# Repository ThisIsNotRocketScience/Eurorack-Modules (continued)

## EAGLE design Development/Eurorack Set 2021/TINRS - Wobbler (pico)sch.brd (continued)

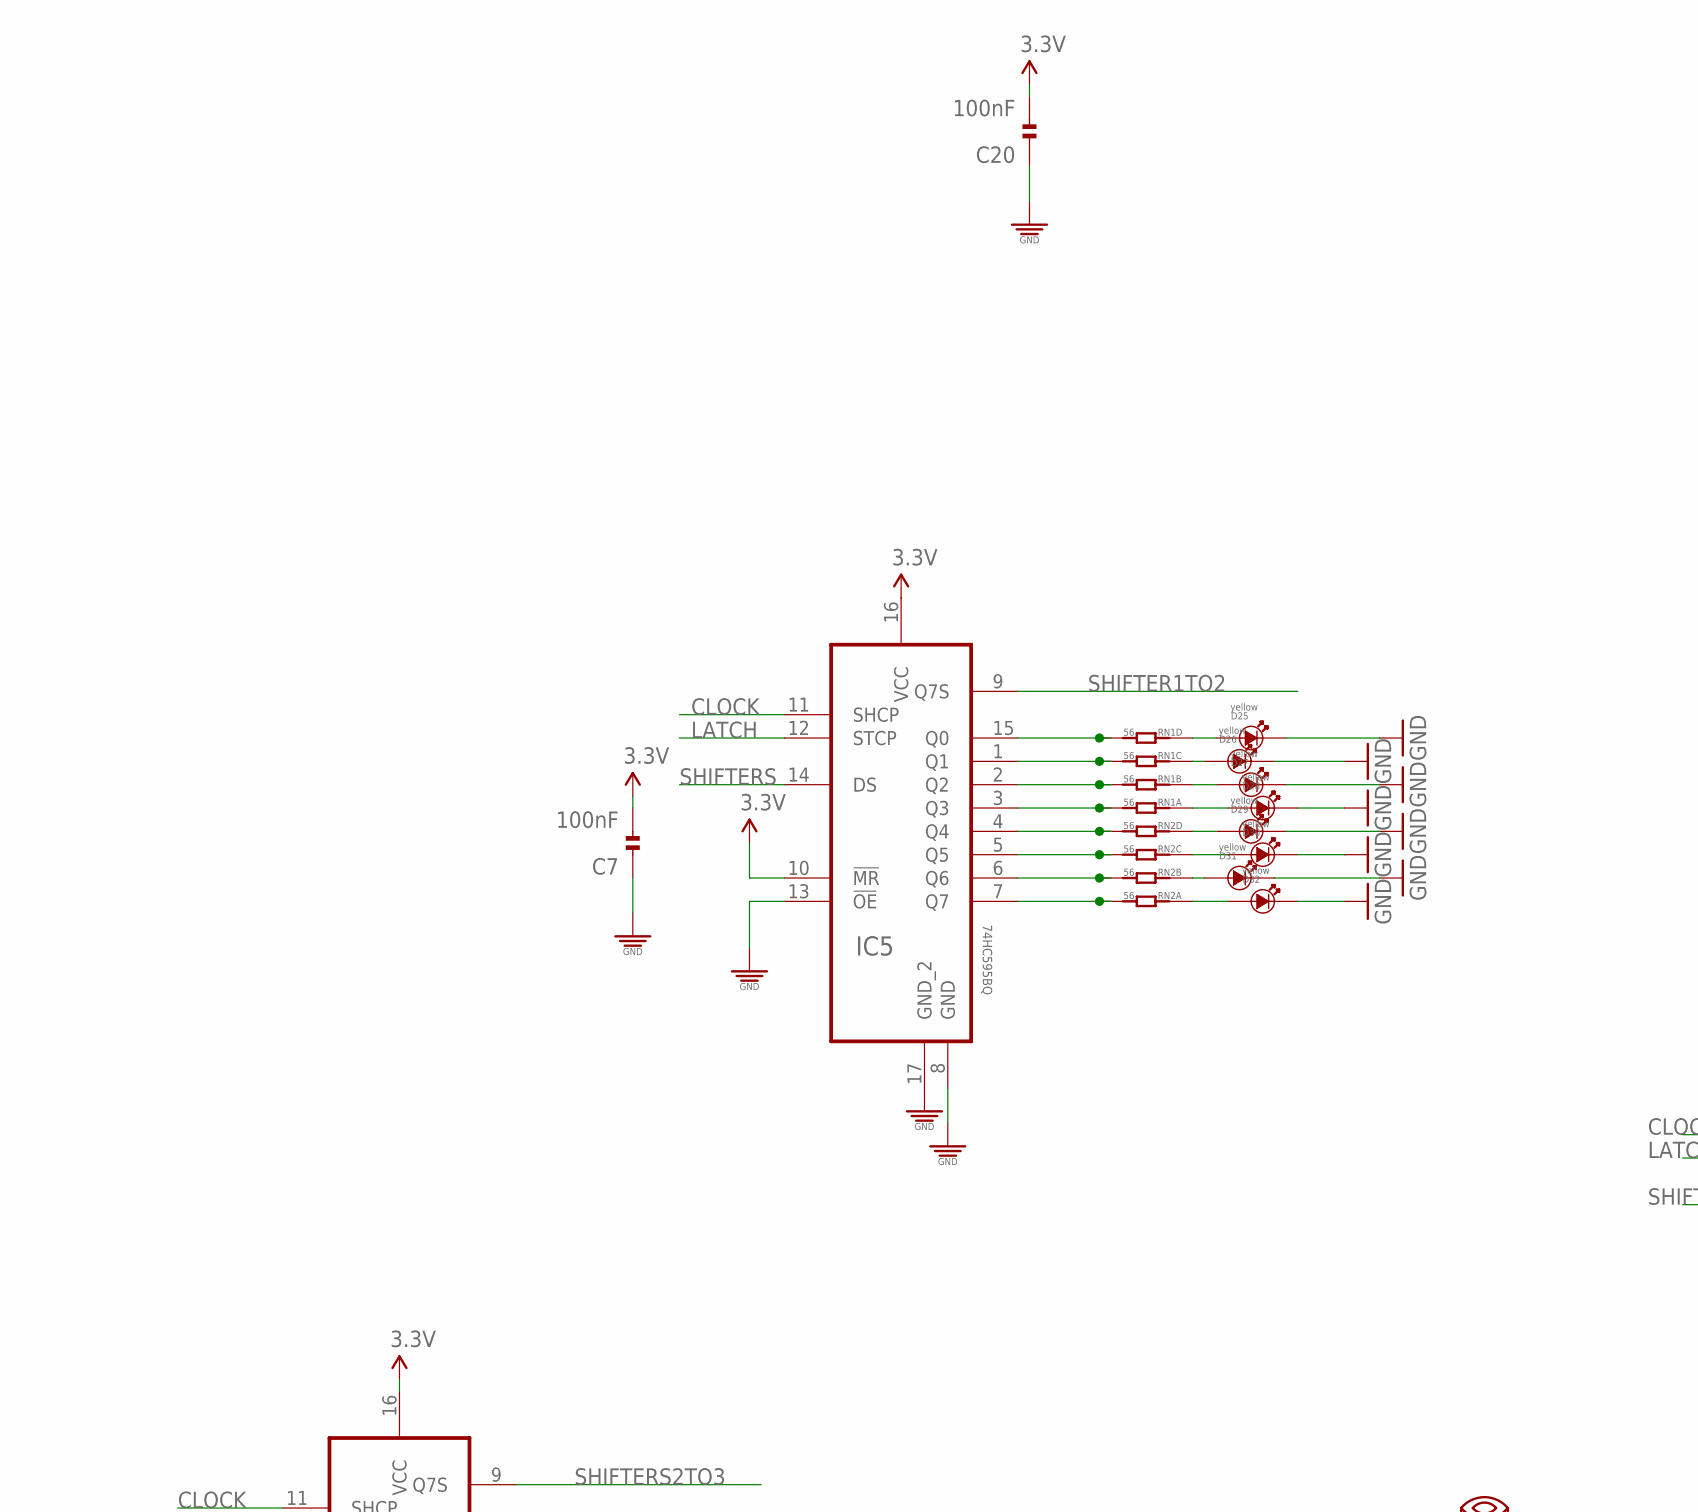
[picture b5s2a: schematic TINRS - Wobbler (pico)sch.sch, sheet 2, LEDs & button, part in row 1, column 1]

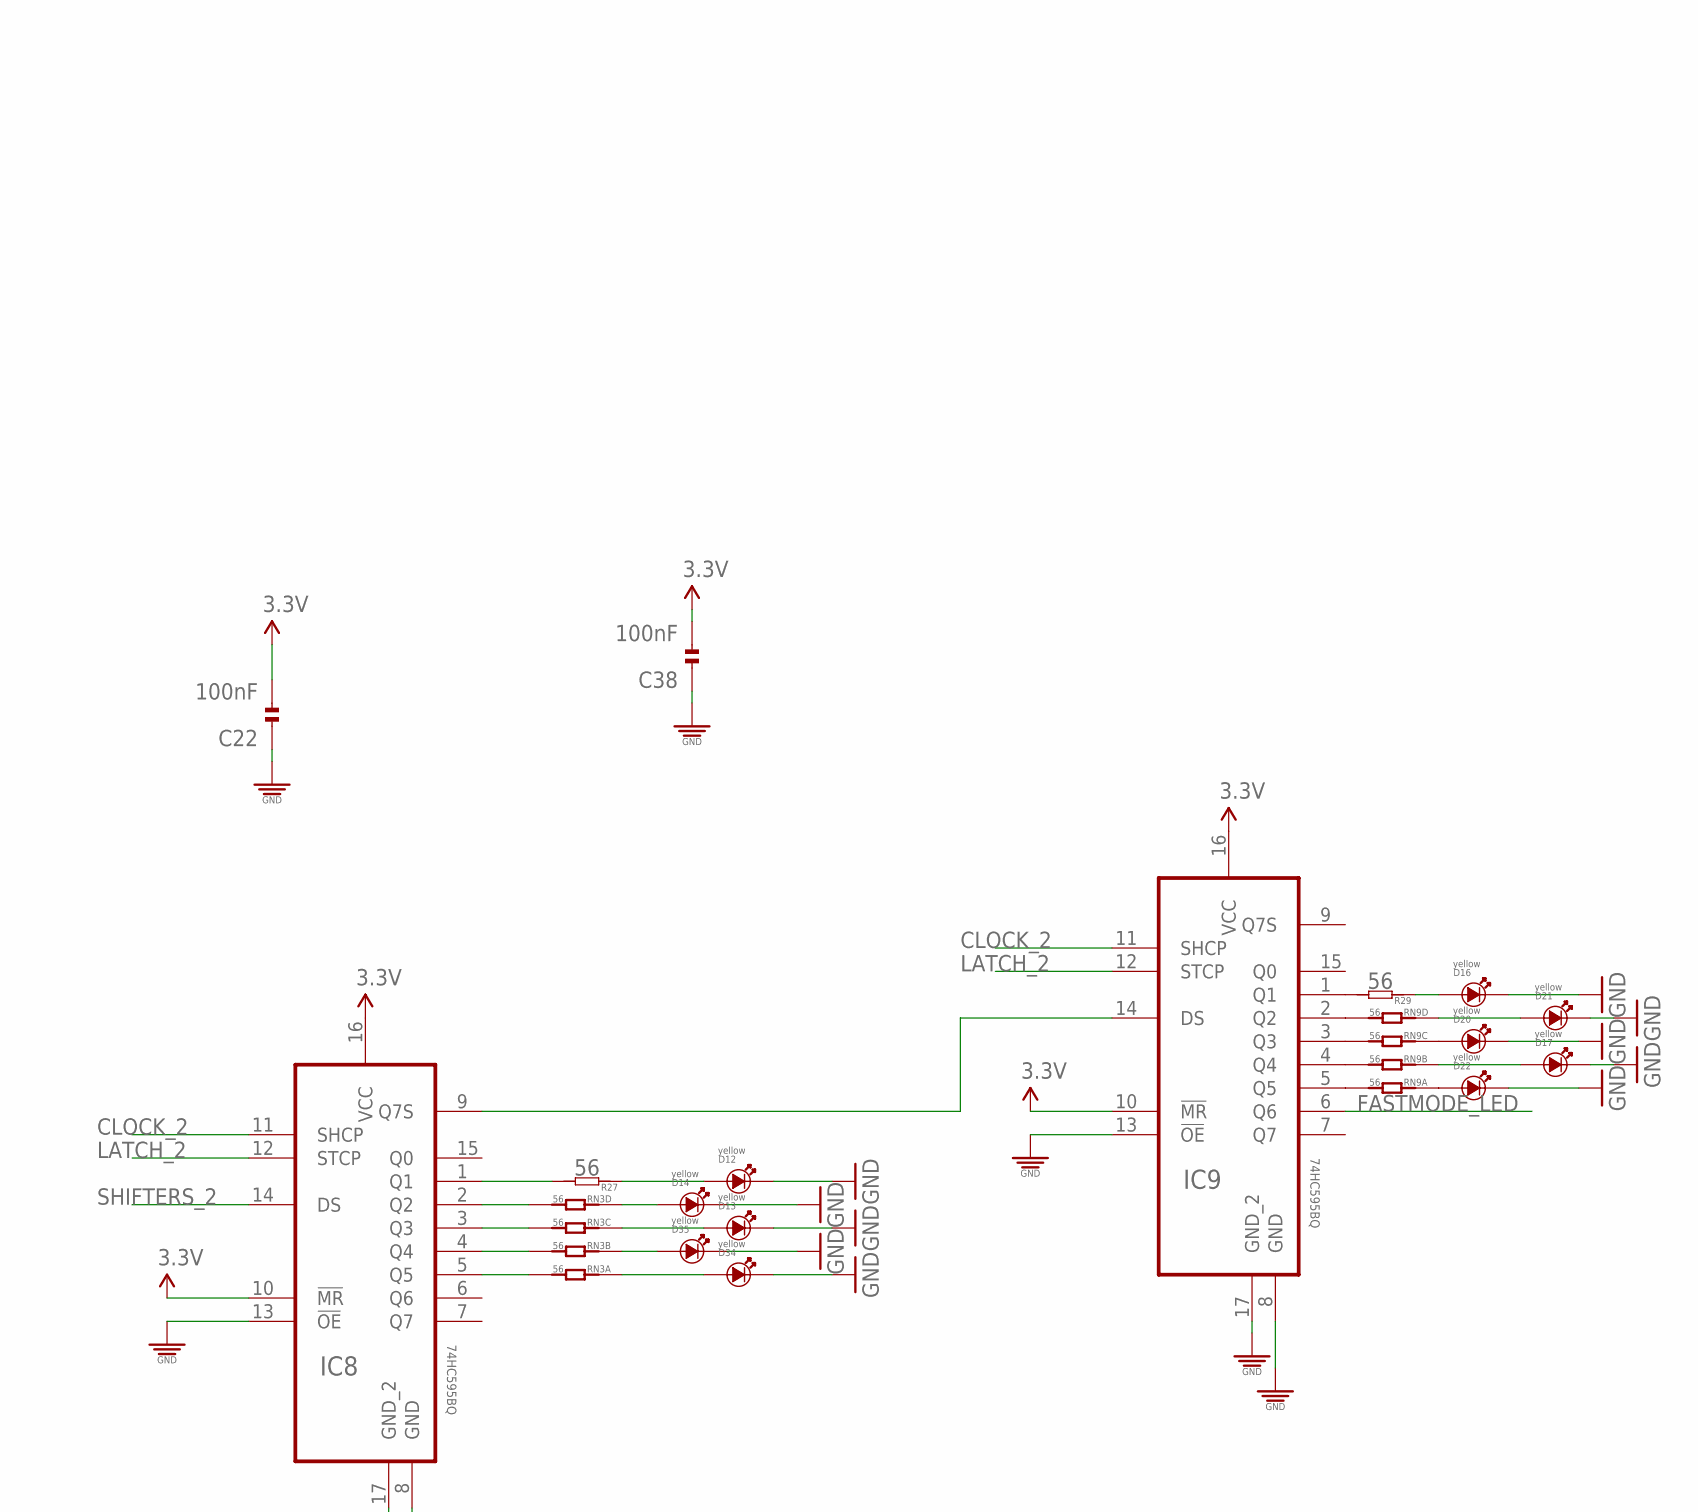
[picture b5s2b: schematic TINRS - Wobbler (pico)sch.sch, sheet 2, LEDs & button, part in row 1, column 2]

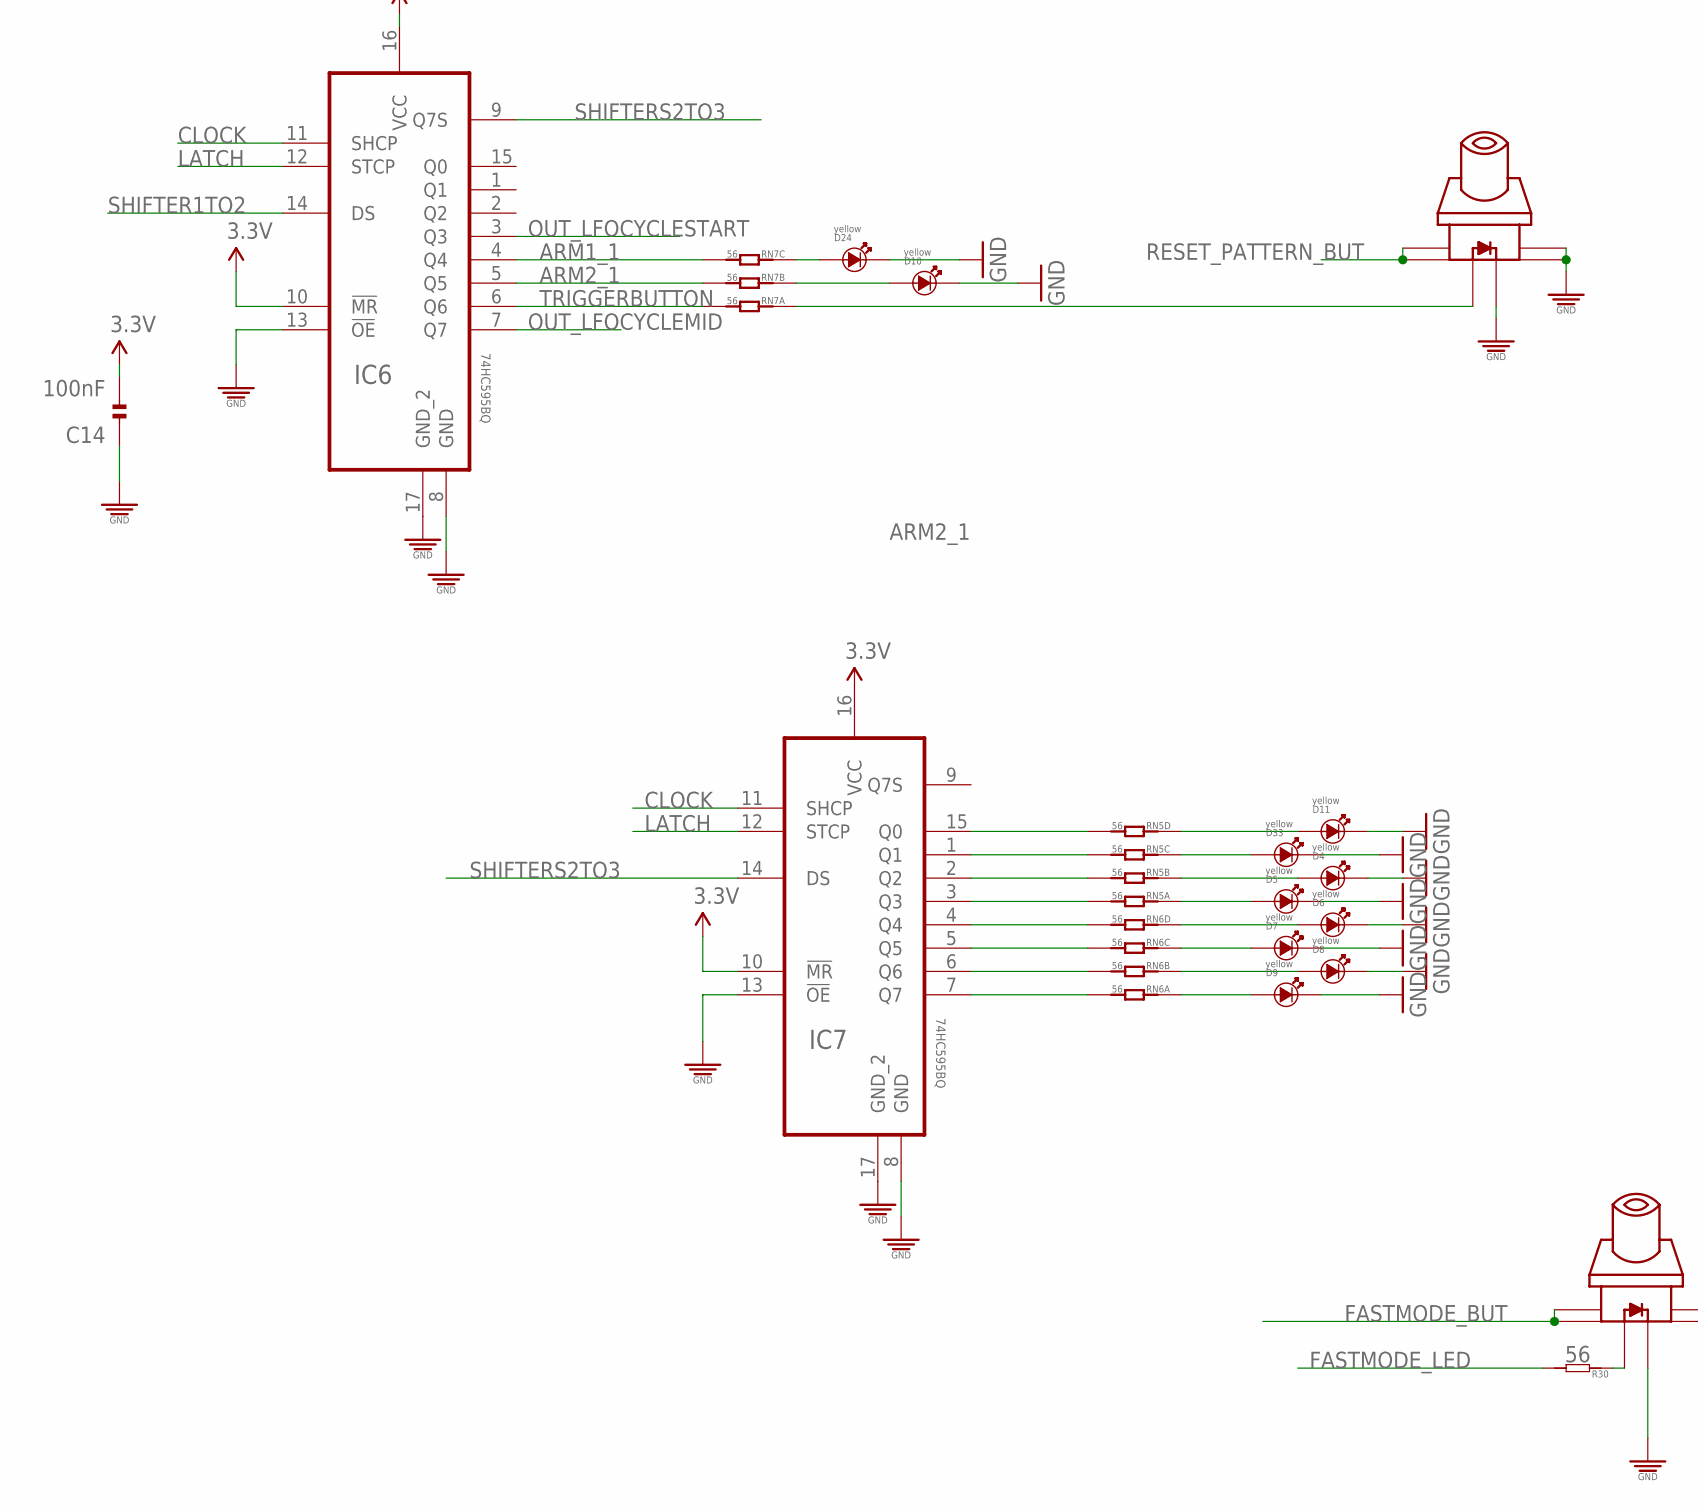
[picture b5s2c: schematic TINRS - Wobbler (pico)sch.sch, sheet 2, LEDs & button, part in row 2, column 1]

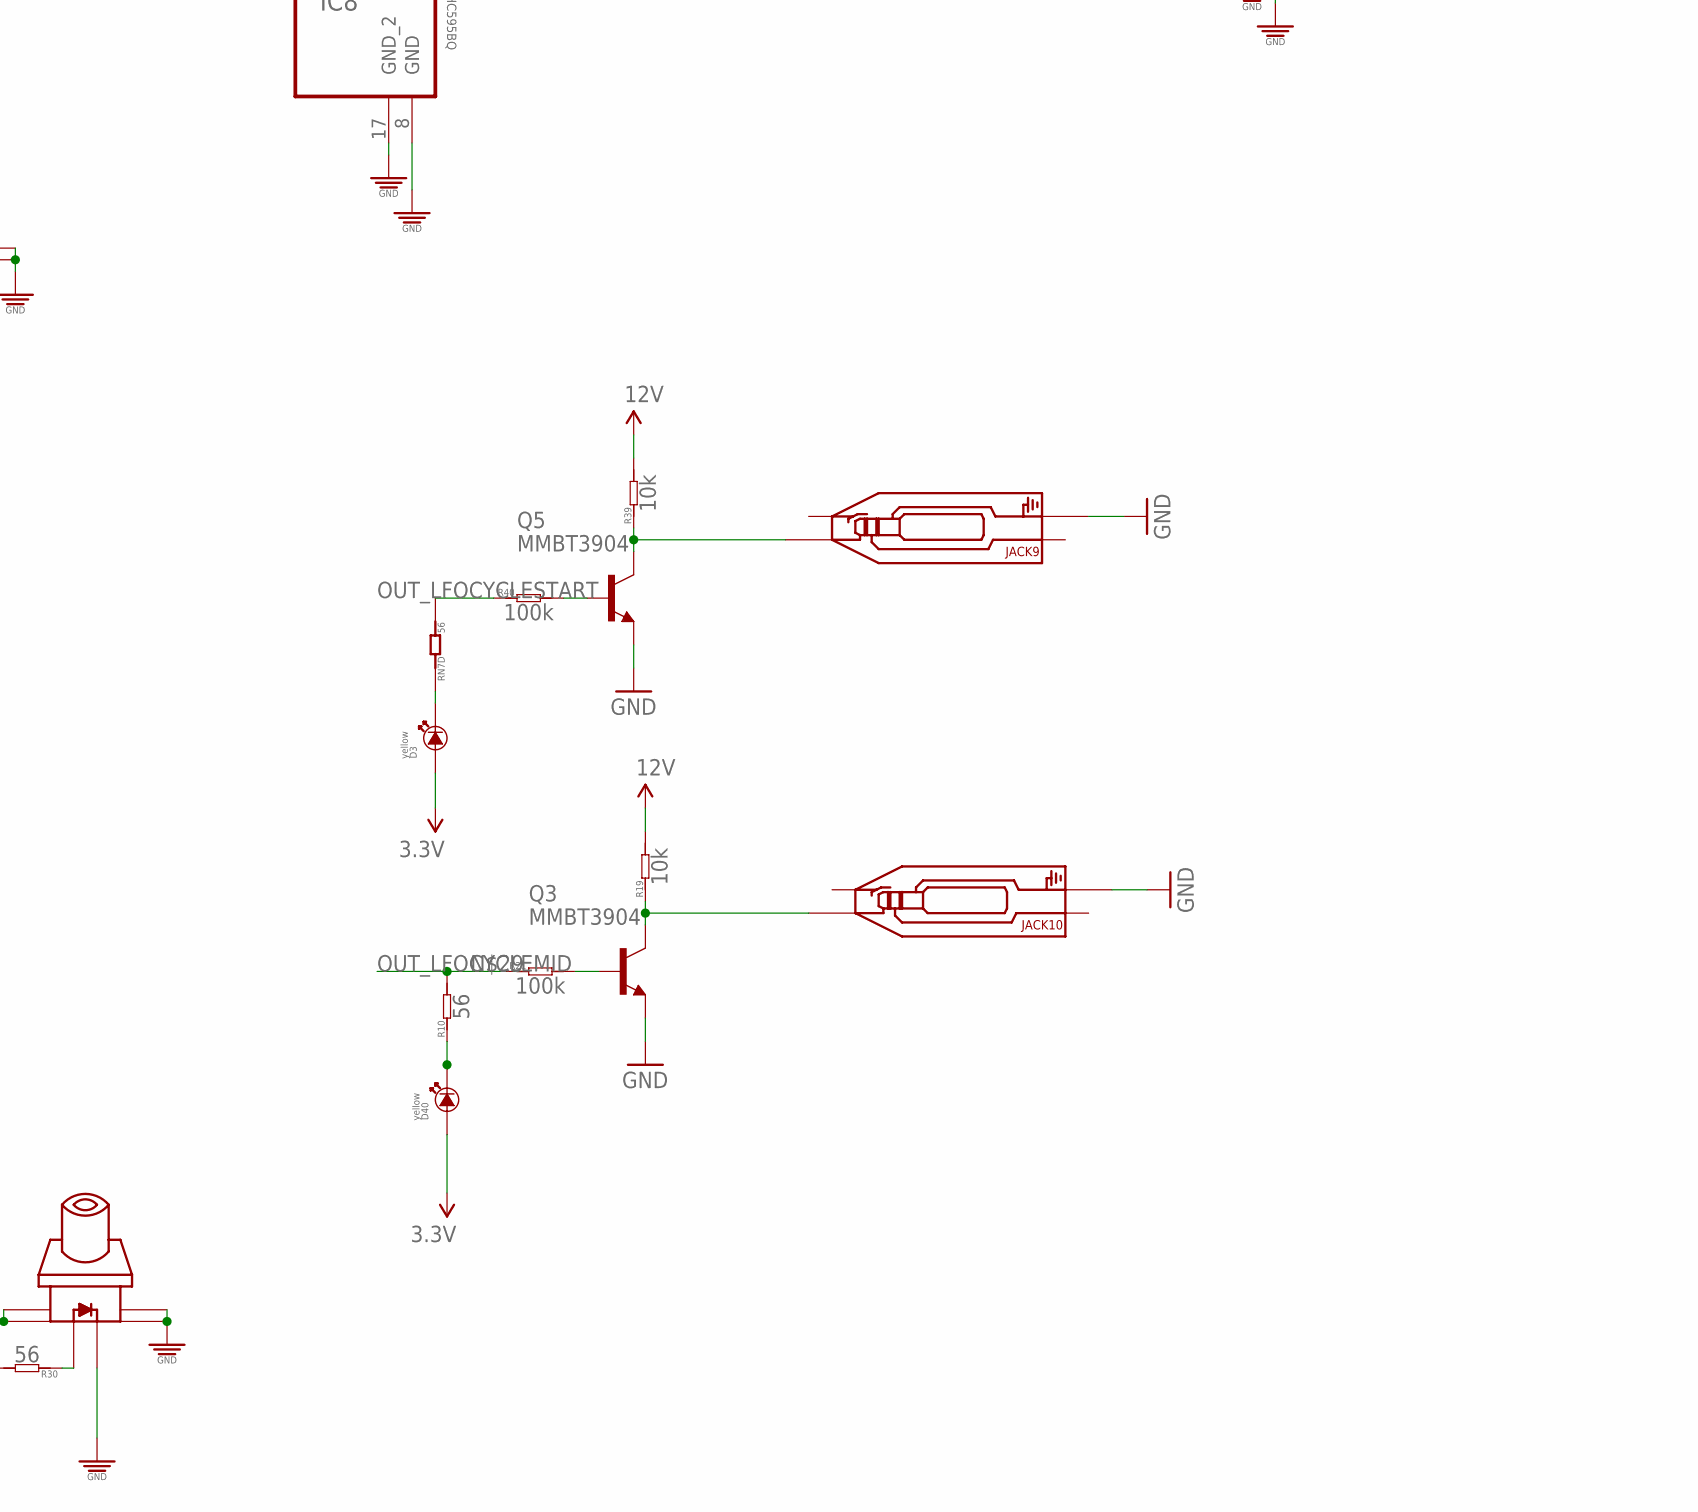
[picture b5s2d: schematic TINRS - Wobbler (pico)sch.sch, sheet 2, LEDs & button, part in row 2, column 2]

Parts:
C7, C14, C20, C22, C38: 100nF; C0402; MPN MC0603F104Z160CT
D3, D4, D5, D6, D7, D8, D9, D10, D11, D12, D13, D14, D16, D17, D20, D21, D22, D24, D25, D26, D27, D28, D29, D30, D31, D32, D33, D34, D35, D40: yellow; 3MMLED
IC5, IC6, IC7, IC8, IC9: 74HC595BQ; QFN50P250X350X100-17N
JACK9, JACK10: AUDIO-JACK_SMALLSYMBOL; 3.5MM-JACK-SWITCH-13MM-NOHOLES-TESTPAD
Q3, Q5: MMBT3904; SOT23-BEC; MPN PMBT3904,215
R10, R27, R29, R30: 56; R0603
R19, R39: 10k; R0603
R21, R40: 100k; R0603
RN1, RN2, RN3, RN5, RN6, RN7, RN9: 56; 4X0402ARV341
U$1, U$28: SWITCH_W_LED_PB6149L-X-102YELLOW; PB6149L

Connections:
3.3V: C7.2, C14.2, C20.2, C22.2, C38.2, D3.+, D40.+, IC5.10 (!MR), IC5.16 (VCC), IC6.10 (!MR), IC6.16 (VCC), IC7.10 (!MR), IC7.16 (VCC), IC8.10 (!MR), IC8.16 (VCC), IC9.10 (!MR), IC9.16 (VCC); also elsewhere on the board
12V: R19.2, R39.2; also elsewhere on the board
ARM1_1: IC6.4 (Q4), RN7.3 (1)
ARM2_1: IC6.5 (Q5), RN7.2 (1)
CLOCK: IC5.11 (SHCP), IC6.11 (SHCP), IC7.11 (SHCP); also elsewhere on the board
CLOCK_2: IC8.11 (SHCP), IC9.11 (SHCP); also elsewhere on the board
FASTMODE_BUT: U$28.1, U$28.2; also elsewhere on the board
FASTMODE_LED: IC9.6 (Q6), R30.2
GND: C7.1, C14.1, C20.1, C22.1, C38.1, D4.-, D5.-, D6.-, D7.-, D8.-, D9.-, D10.-, D11.-, D12.-, D13.-, D14.-, D16.-, D17.-, D20.-, D21.-, D22.-, D24.-, D25.-, D26.-, D27.-, D28.-, D29.-, D30.-, D31.-, D32.-, D33.-, D34.-, D35.-, IC5.8 (GND), IC5.13 (!OE), IC5.17 (GND_2), IC6.8 (GND), IC6.13 (!OE), IC6.17 (GND_2), IC7.8 (GND), IC7.13 (!OE), IC7.17 (GND_2), IC8.8 (GND), IC8.13 (!OE), IC8.17 (GND_2), IC9.8 (GND), IC9.13 (!OE), IC9.17 (GND_2), JACK9.RING_B@1 (RING), JACK9.RING_T@3 (RING), JACK10.RING_B@1 (RING), JACK10.RING_T@3 (RING), Q3.E, Q5.E, U$1.3, U$1.4, U$1.LEDNEG (NEG), U$28.3, U$28.4, U$28.LEDNEG (NEG); also elsewhere on the board
LATCH: IC5.12 (STCP), IC6.12 (STCP), IC7.12 (STCP); also elsewhere on the board
LATCH_2: IC8.12 (STCP), IC9.12 (STCP); also elsewhere on the board
unnamed: IC5.15 (Q0), RN1.4 (1)
unnamed: D7.+, RN6.6 (2)
unnamed: IC5.1 (Q1), RN1.3 (1)
unnamed: IC5.2 (Q2), RN1.2 (1)
unnamed: D40.-, R10.1
unnamed: Q3.B, R21.2
unnamed: IC5.3 (Q3), RN1.1
unnamed: D3.-, RN7.5 (2)
unnamed: D29.+, RN2.5 (2)
unnamed: JACK10.TIP_B@1 (TIP), JACK10.TIP_T@3 (TIP), Q3.C, R19.1
unnamed: IC5.4 (Q4), RN2.4 (1)
unnamed: IC5.5 (Q5), RN2.3 (1)
unnamed: D28.+, RN1.8 (2)
unnamed: IC5.6 (Q6), RN2.2 (1)
unnamed: IC5.7 (Q7), RN2.1
unnamed: IC8.2 (Q2), RN3.4 (1)
unnamed: IC7.7 (Q7), RN6.1
unnamed: IC7.6 (Q6), RN6.2 (1)
unnamed: IC7.5 (Q5), RN6.3 (1)
unnamed: D10.+, RN7.7 (2)
unnamed: D13.+, RN3.6 (2)
unnamed: IC7.4 (Q4), RN6.4 (1)
unnamed: D6.+, RN6.5 (2)
unnamed: D5.+, RN5.8 (2)
unnamed: D4.+, RN5.7 (2)
unnamed: D8.+, RN6.7 (2)
unnamed: D9.+, RN6.8 (2)
unnamed: RN7.8 (2), U$1.LEDPOS (POS)
unnamed: D11.+, RN5.5 (2)
unnamed: IC7.3 (Q3), RN5.1
unnamed: IC7.2 (Q2), RN5.2 (1)
unnamed: IC7.1 (Q1), RN5.3 (1)
unnamed: IC7.15 (Q0), RN5.4 (1)
unnamed: IC8.3 (Q3), RN3.3 (1)
unnamed: D14.+, RN3.5 (2)
unnamed: IC8.4 (Q4), RN3.2 (1)
unnamed: Q5.B, R40.2
unnamed: JACK9.TIP_B@1 (TIP), JACK9.TIP_T@3 (TIP), Q5.C, R39.1
unnamed: IC8.5 (Q5), RN3.1
unnamed: IC8.1 (Q1), R27.2
unnamed: D12.+, R27.1
unnamed: D34.+, RN3.8 (2)
unnamed: D35.+, RN3.7 (2)
unnamed: IC9.5 (Q5), RN9.1
unnamed: R30.1, U$28.LEDPOS (POS)
unnamed: D20.+, RN9.6 (2)
unnamed: D30.+, RN2.6 (2)
unnamed: D31.+, RN2.7 (2)
unnamed: D32.+, RN2.8 (2)
unnamed: D24.+, RN7.6 (2)
unnamed: D27.+, RN1.7 (2)
unnamed: D26.+, RN1.6 (2)
unnamed: D25.+, RN1.5 (2)
unnamed: D33.+, RN5.6 (2)
unnamed: D16.+, R29.1
unnamed: D21.+, RN9.5 (2)
unnamed: D17.+, RN9.7 (2)
unnamed: D22.+, RN9.8 (2)
unnamed: IC9.4 (Q4), RN9.2 (1)
unnamed: IC9.3 (Q3), RN9.3 (1)
unnamed: IC9.2 (Q2), RN9.4 (1)
unnamed: IC9.1 (Q1), R29.2
unnamed: IC8.9 (Q7S), IC9.14 (DS)
OUT_LFOCYCLEMID: IC6.7 (Q7), R10.2, R21.1
OUT_LFOCYCLESTART: IC6.3 (Q3), R40.1, RN7.4 (1)
RESET_PATTERN_BUT: U$1.1, U$1.2; also elsewhere on the board
SHIFTER1TO2: IC5.9 (Q7S), IC6.14 (DS)
SHIFTERS: IC5.14 (DS); also elsewhere on the board
SHIFTERS2TO3: IC6.9 (Q7S), IC7.14 (DS)
SHIFTERS_2: IC8.14 (DS); also elsewhere on the board
TRIGGERBUTTON: IC6.6 (Q6), RN7.1

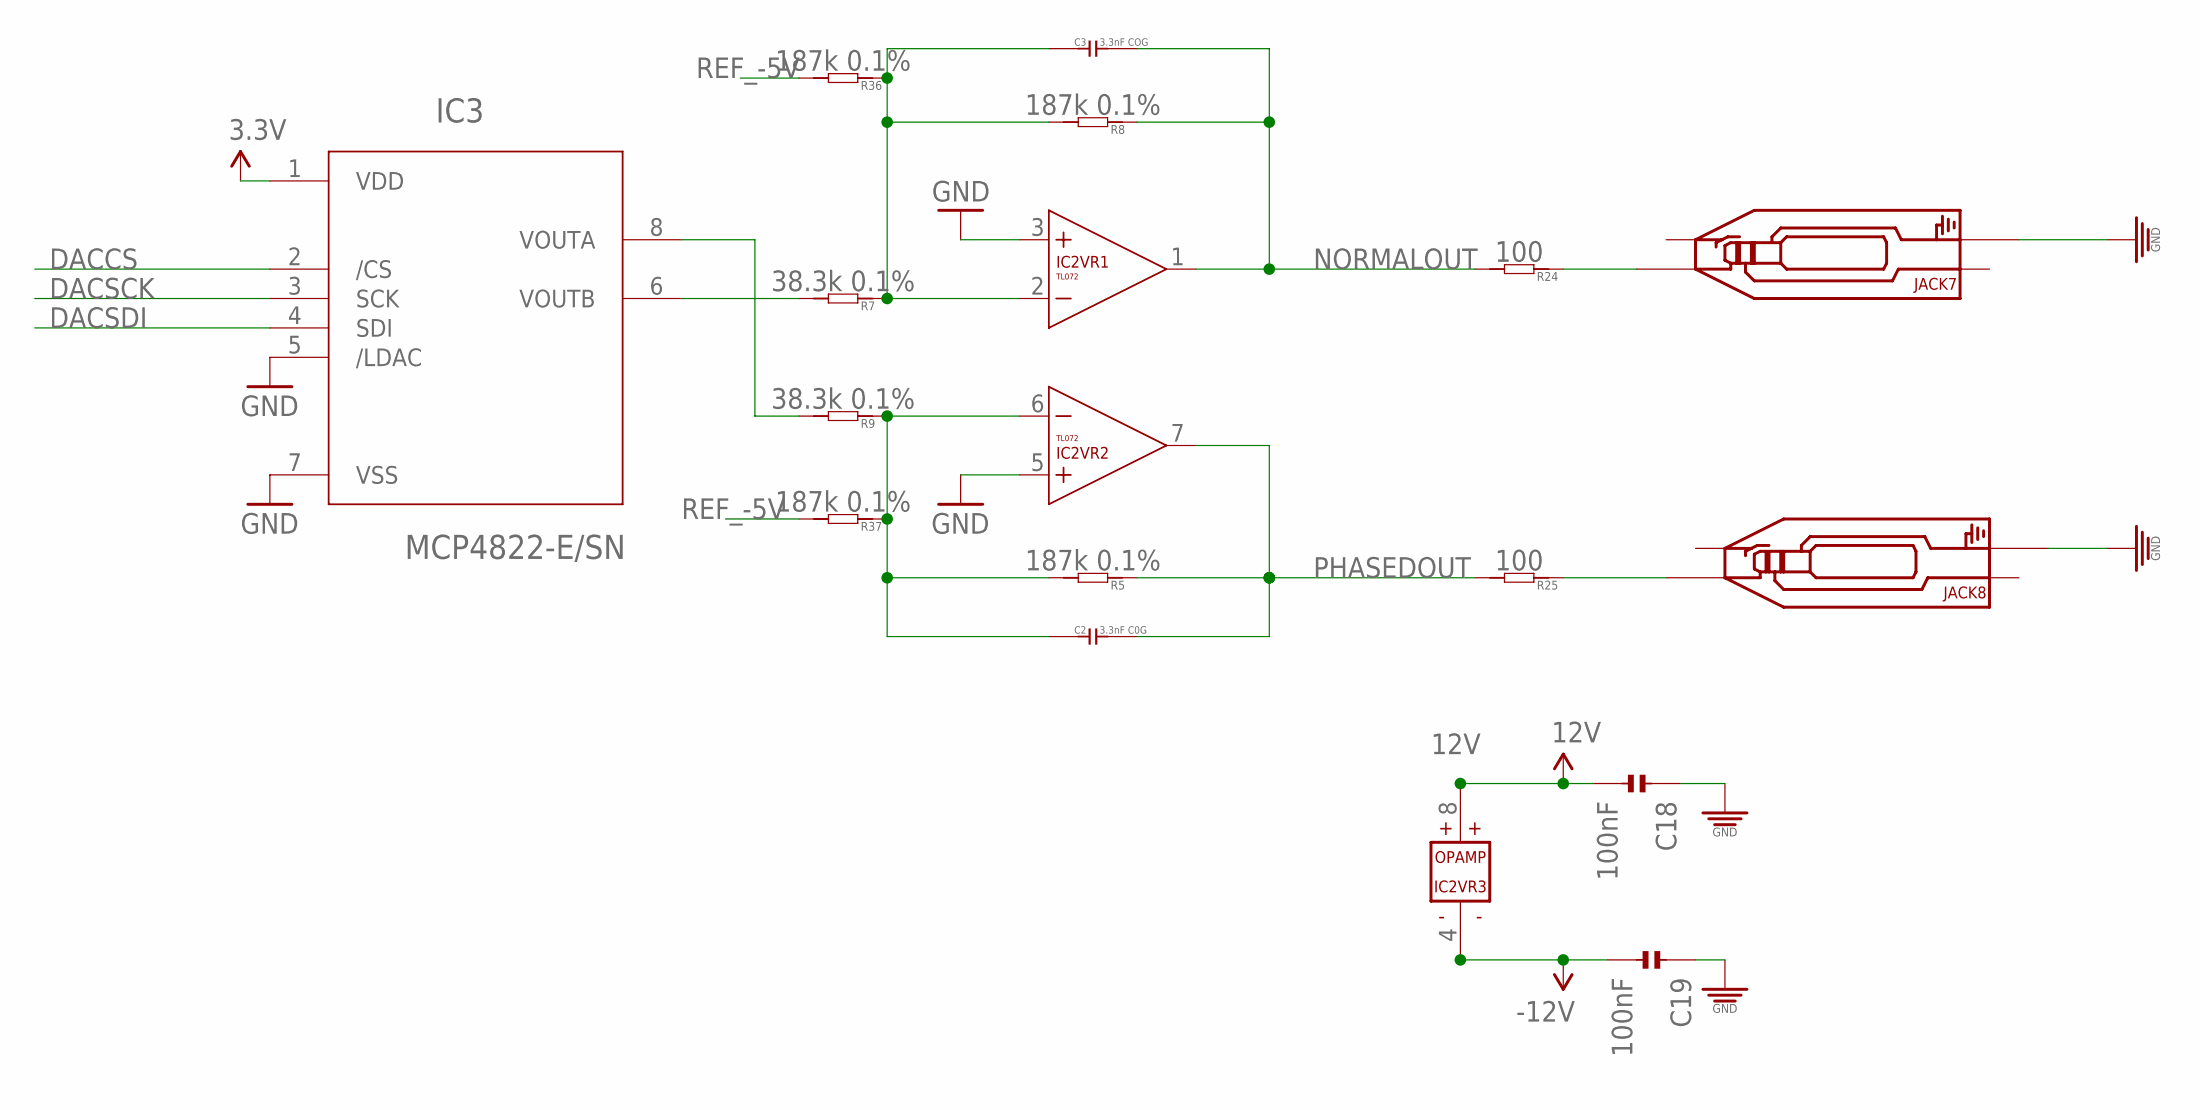
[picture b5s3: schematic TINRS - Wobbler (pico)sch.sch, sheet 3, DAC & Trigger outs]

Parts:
C2: 3.3nF C0G; C0603
C3: 3.3nF COG; C0603
C18, C19: 100nF; C0402; MPN MC0603F104Z160CT
IC2: TL072; SO08
IC3: MCP4822-E/SN; SOIC8-N_MC
JACK7, JACK8: AUDIO-JACK_SMALLSYMBOL; 3.5MM-JACK-SWITCH-13MM-NOHOLES-TESTPAD
R5, R8, R36, R37: 187k 0.1%; R0603
R7, R9: 38.3k 0.1%; R0603
R24, R25: 100; R0603

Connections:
3.3V: IC3.1 (VDD); also elsewhere on the board
12V: C18.2, IC2.8 (V+); also elsewhere on the board
-12V: C19.2, IC2.4 (V-); also elsewhere on the board
DACCS: IC3.2 (/CS); also elsewhere on the board
DACSCK: IC3.3 (SCK); also elsewhere on the board
DACSDI: IC3.4 (SDI); also elsewhere on the board
GND: C18.1, C19.1, IC2.3 (+IN), IC2.5 (+IN), IC3.5 (/LDAC), IC3.7 (VSS), JACK7.RING_B@1 (RING), JACK7.RING_T@3 (RING), JACK8.RING_B@1 (RING), JACK8.RING_T@3 (RING); also elsewhere on the board
unnamed: IC3.8 (VOUTA), R9.2
unnamed: IC3.6 (VOUTB), R7.2
unnamed: C2.1, IC2.6 (-IN), R5.2, R9.1, R37.1
unnamed: C3.1, IC2.2 (-IN), R7.1, R8.2, R36.1
unnamed: JACK8.TIP_B@1 (TIP), JACK8.TIP_T@3 (TIP), R25.1
unnamed: JACK7.TIP_B@1 (TIP), JACK7.TIP_T@3 (TIP), R24.1
NORMALOUT: C3.2, IC2.1 (OUT), R8.1, R24.2
PHASEDOUT: C2.2, IC2.7 (OUT), R5.1, R25.2
REF_-5V: R36.2, R37.2; also elsewhere on the board

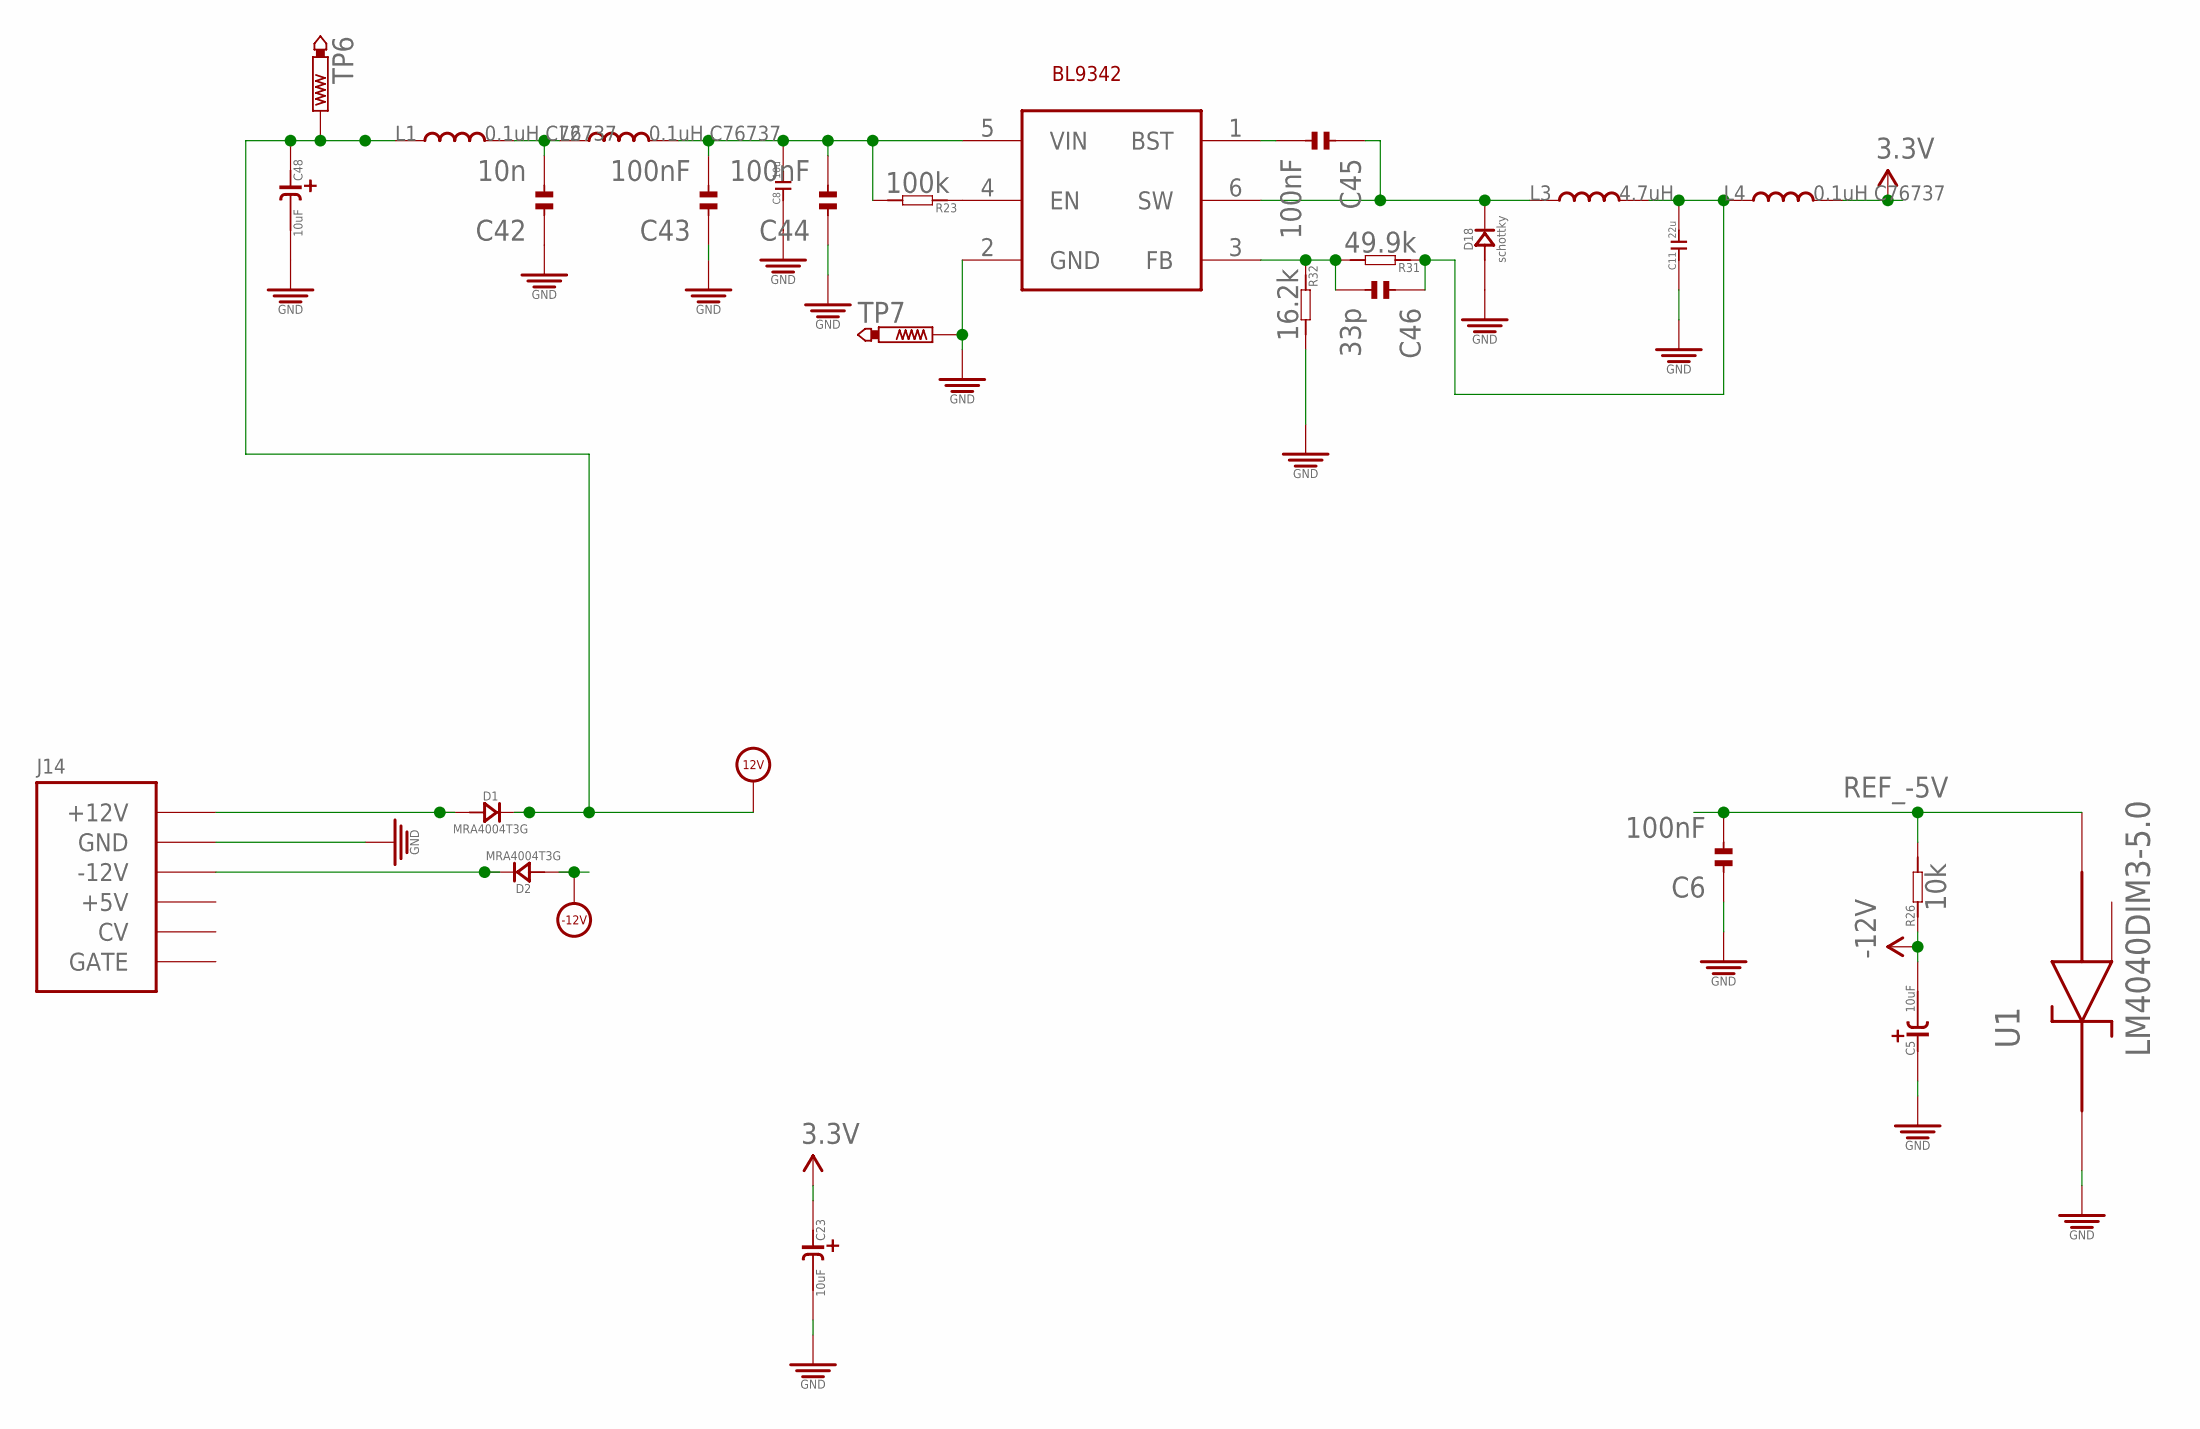
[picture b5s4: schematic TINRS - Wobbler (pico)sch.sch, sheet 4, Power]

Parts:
C5, C23, C48: 10uF; CASE-A_3216; MPN TAJB106K020RNJ
C6: 100nF; C0402; MPN 06035C104KAT2A
C8: 10u; C0805
C11: 22u; C0805
C42: 10n; C0402; MPN MC0603F104Z160CT
C43, C44, C45: 100nF; C0402; MPN MC0603F104Z160CT
C46: 33p; C0402; MPN MC0603F104Z160CT
D1, D2: MRA4004T3G; DO-214AC; MPN US1G-E3/5AT
D18: schottky; SOD123
J14: POWERSHROUDED; POWER_16_SHROUDED
L1, L2, L4: 0.1uH C76737; L0805
L3: 4.7uH; L0420
R23: 100k; R0603
R26: 10k; R0603
R31: 49.9k; R0603
R32: 16.2k; R0603
TP6, TP7: PTR1B1,27; B1,27
U1: LM4040DIM3-5.0; SOT95P237X112-3N
U$5: BL9342; SOT23-6

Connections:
3.3V: C23.+ (1), L4.2; also elsewhere on the board
12V: C48.+ (1), D1.2 (-), L1.1, TP6.TP; also elsewhere on the board
-12V: C5.- (2), D2.1 (+), R26.1; also elsewhere on the board
GND: C5.+ (1), C6.1, C8.1, C11.1, C23.- (2), C42.1, C43.1, C44.1, C48.- (2), D18.+, J14.3 (GND), J14.4 (GND), J14.5 (GND), J14.6 (GND), J14.7 (GND), J14.8 (GND), R32.2, TP7.TP, U1.1 (CATHODE), U$5.2 (GND); also elsewhere on the board
unnamed: D1.1 (+), J14.9 (+12V), J14.10 (+12V)
unnamed: D2.2 (-), J14.1 (-12V), J14.2 (-12V)
unnamed: C42.2, L1.2, L2.1
unnamed: C8.2, C43.2, C44.2, L2.2, R23.2, U$5.5 (VIN)
unnamed: C45.2, U$5.1 (BST)
unnamed: C45.1, D18.-, L3.1, U$5.6 (SW)
unnamed: C46.2, R31.2, R32.1, U$5.3 (FB)
unnamed: C11.2, C46.1, L3.2, L4.1, R31.1
unnamed: R23.1, U$5.4 (EN)
REF_-5V: C6.2, R26.2, U1.2 (ANODE); also elsewhere on the board
